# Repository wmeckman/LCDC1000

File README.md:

# LCDC1000
An ESP32 based controller that can drive any kind of LED strip, or motor. Includes microSD, USB-UART, and large voltage range input.

This project started as a Wifi and bluetooth controller that could drive any type of LED strip. LED strip controllers are everywhere, but I wanted a controller that I could customize without using a breadboard. As the project progressed, I wanted this board to be able to drive motors as well. I added a microSD card for file storage, and a USB-UART for debug. Here are the main features:

ESP32 based using MicroPython
Drives Any type of LED strip - RGB, RGBW, WS2812, APA102, Neopixel, etc
Wide input power range: 4.5V to 30V DC.
Input power via Barrel Jack 2.10mm ID (0.083"), 5.50mm OD or Terminal Block.
Reverse polarity input power protection.
Drives 1 stepper motor in full H-bridge configuration.
Drives 2 bipolar DC motors in half H-bridge configuration.
Drives 4 Unipolar DC Motors.
Additional outputs for servo motors available.
Current sense for motor/LED drivers.
Outputs on terminal blocks.

Power: 4.5V-30V DC power can be applied either through the barrel jack or the terminal block (not both). An on-board regulator is used to create the 3.3V necessary for the ESP32, MicroUSB, and USB-UART.  The power input on J6 and J5 is equal to the power output on J7.  Use a power supply that is designed to drive what is connected on the output.  For example, if driving a 12V RGB LED strip, use a 12V power supply.  

To use the board, connect whatever you're controlling (LED, motor, etc) to the terminal blocks (J3, J4, J7), then apply power to J5 or J6.  The 'connection notes' section provides more in depth instruction by device.

Pinouts

J6 Barrel Jack Input Power

    Pin:  +Vin 4.5V to 30V
    Shield:  Ground

J5 Input Power Terminal Block

    1:  +Vin 4.5V to 30V
    2:  +Vin 4.5V to 30V
    3:  Ground
    4:  Ground

J7 Output Power Terminal Block

    1:  +Vout
    2:  +Vout
    3:  Ground
    4:  Ground

J3, J4, J8 High Current Motor and RGB, RGBW LED Drive Terminal Block

    J3-1:  Power Out
    J3-8:  Drive1Out1
    J4-1:  Drive1Out2
    J4-2:  Drive2Out1
    J8-1:  Drive2Out2
    J8-2:  Ground

J9 and J10:  SPI, and PWM Drive Signals for Servo Motor, individually addressable LED's Terminal Block

    J9-1:  GPIO_2 (ESP32 IO2)
    J9-2:  GPIO_5 (ESP32 IO5) 
    J10-1:  LED_DATA (ESP IO19)
    J10-2:  LED_CLK (ESP IO18)

Test Point Header Pins

    TP1:  TDI_SD_MISO - Primarily used to SD card, but can be used for JTAG
    TP2:  TDO_SD_CD - Primarily used to SD card, but can be used for JTAG
    TP3:  TMS_SD_CLK - Primarily used to SD card, but can be used for JTAG
    TP4:  TCK_SD_MOSI - Primarily used to SD card, but can be used for JTAG
    TP5:  ESP32 Enable
    TP7:  IO17
    TP8:  GPIO_0 - ESP32 IO0
    TP9:  ESP32 IO35
    TP10:  ESP32 SENSOR_VP
    TP11:  ESP32 SENSOR_VN
    TP12:  +Vout
    TP13:  +Vout
    TP14:  +Vout
    TP17:  GND
    TP18:  GND
    TP19:  GND
    USBPWR_TP:  USB Power 

Note:  TP2, TP7, TP8 are arranged on the PCB with TP12-TP14, and TP17-TP19 to be compatible with servo motor connections.

---------------------------------------------------------------------------------------------------

Connection Notes:  Overview of connections for various devices

Individually addressable LED's - WS2812, NeoPixel, etc.

    J7-1:  LED Power
    J7-4:  LED Ground
    J9-1:  LED Data

Individually Addressable LED's - APA102, SK9822, DotStar, etc.

    J7-1:  LED Power
    J7-4:  LED Ground
    J10-1:  LED Data
    J10-2:  LED Clock

J10-1, and J10-2 are connected to the ESP32 SPI bus.  This provides the highest speed possible.  Additional LED strips can be connected using lower speed GPIO pins.  

Low speed GPIO connection example:

    J7-2:  LED Power
    J7-3:  LED Ground
    J9-1:  LED Data
    J9-2:  LED Clock

RGB Strips

    J7-1: LED Power
    J3-1: R
    J3-2: G
    J3-3: B

RGBW Strips

    J3-1: LED Power
    J3-2: R
    J4-1: G
    J4-2: B
    J8-1: W

Bipolar DC Stepper Motor

    J3-2:  Coil1+
    J4-1:  Coil1-
    J4-2:  Coil2+
    J8-1:  Coil2-

Unipolar DC Stepper Motor 5 Wire

    J3-2:  Coil 1
    J4-1:  Coil 2
    J4-2:  Coil 3
    J8-1:  Coil 4
    J7-3:  Ground

Unipolar DC Stepper Motor 6 Wire

    J3-2:  Coil 1
    J4-1:  Coil 2
    J4-2:  Coil 3
    J8-1:  Coil 4
    J7-3:  Ground
    J7-4:  Ground

DC Motor Unidirectional  :  Connect up to 4

    Use J3-2 or J4-1 or J4-2 or J8-1 for (+) wire
    Use J7-3 or J7-4 for (-) wire

DC Bidirectional Motor  :  Connect up to 2

    J3-2: Motor 1 (+) 
    J4-1: Motor 1 (-)
    J4-2: Motor 2 (+) 
    J8-1: Motor 2 (-)

Servo Motors

    J7-1 Servo 1 Power +
    J7-3 Servo 1 Power -
    J9-1 Servo 1 Control

    J7-2 Servo 2 Power +
    J7-4 Servo 2 Power -
    J9-2 Servo 2 Control

Additional Servos can be connected on the header pins.

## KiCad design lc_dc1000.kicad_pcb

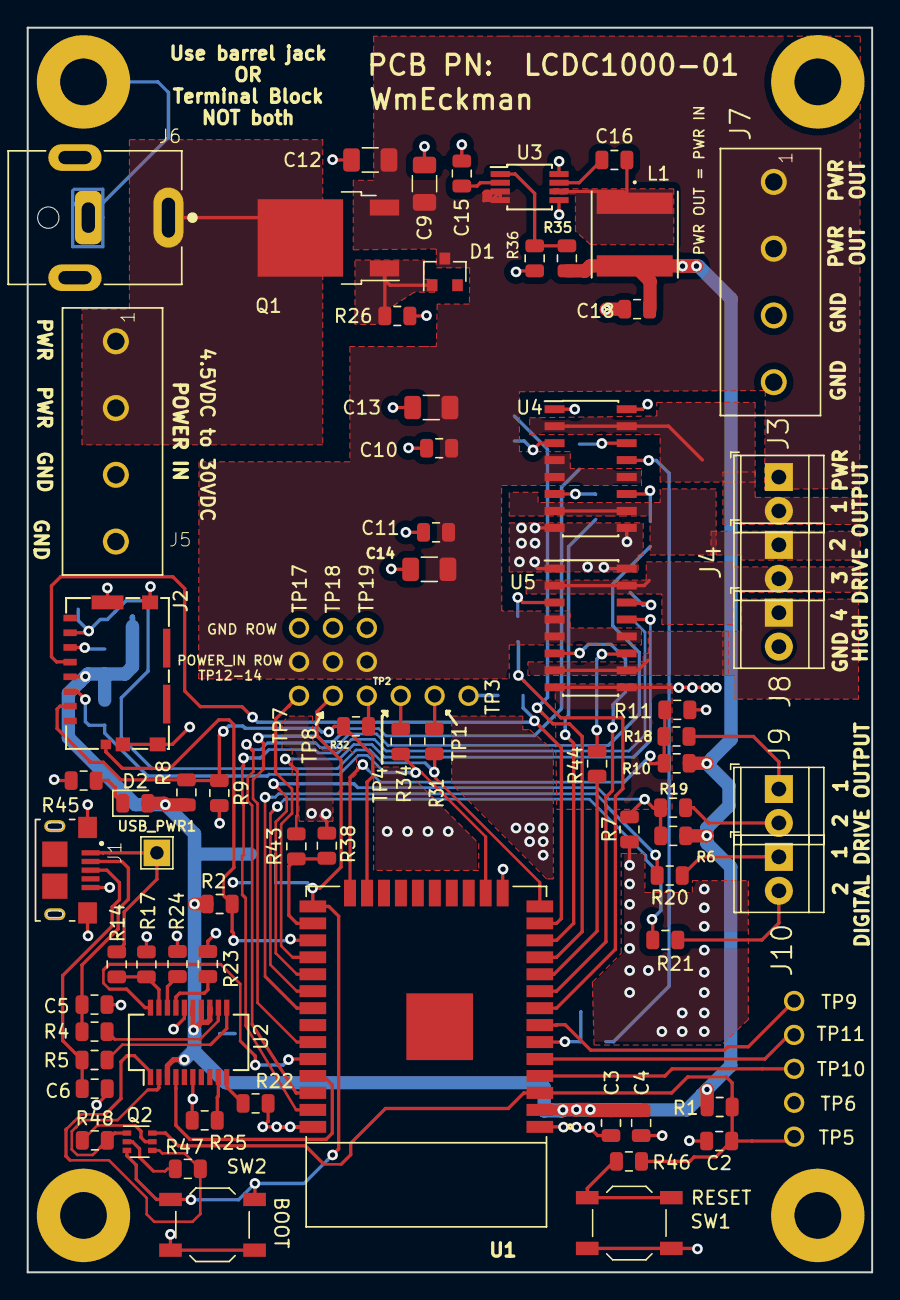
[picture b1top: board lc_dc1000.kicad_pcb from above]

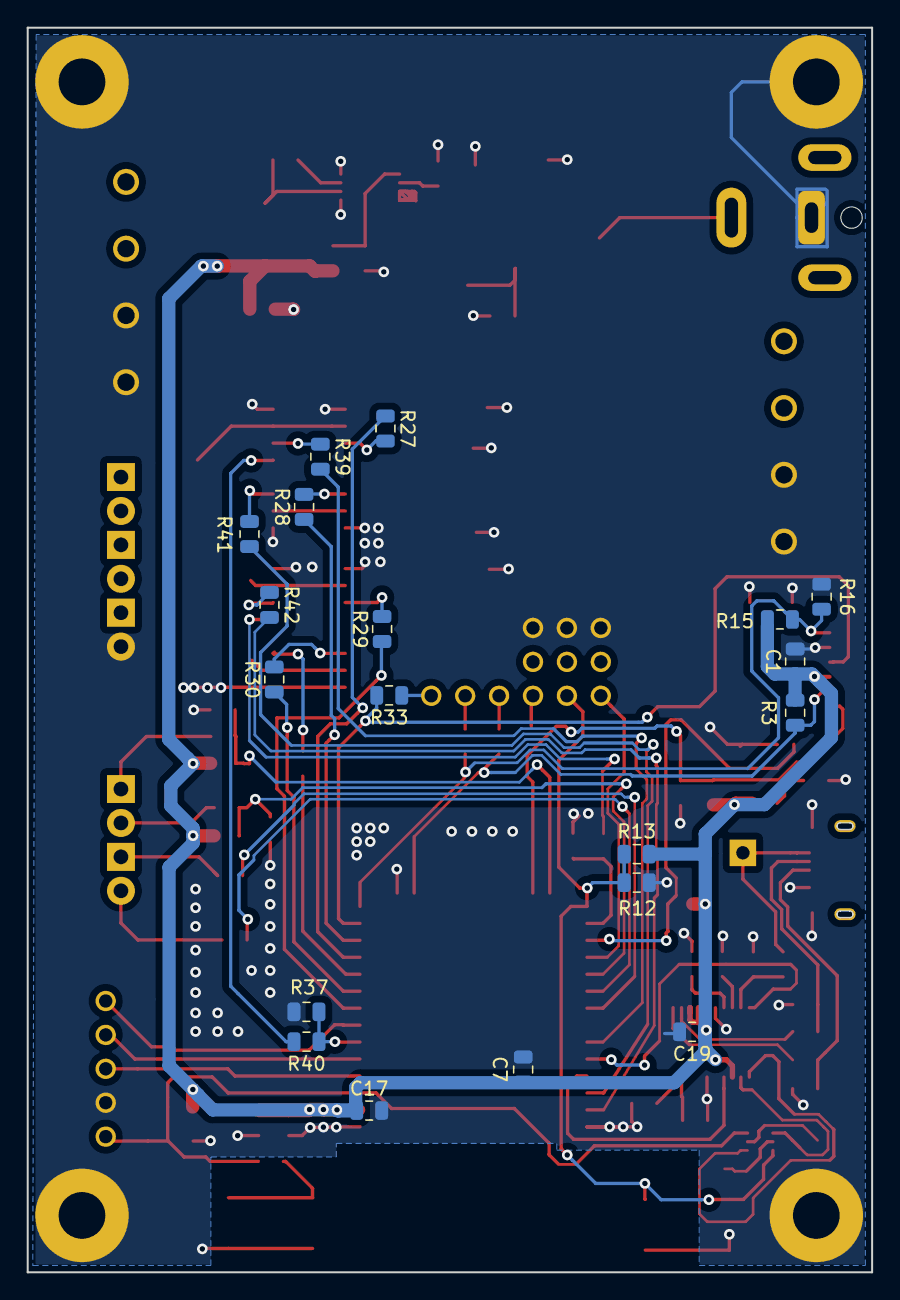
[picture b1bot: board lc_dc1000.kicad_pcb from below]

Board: 2 copper layers, 63.2 x 93.2 mm, 110 parts (19 on the bottom side), 74 nets.

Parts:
C1, C2, C3, C7, C10, C11: 0.1uF; C_0805_2012Metric
C4, C17, C18, C19: 10uF; C_0805_2012Metric
C5, C6: 27pF; C_0805_2012Metric
C9, C12, C13, C14: 4.7uF; C_1206_3216Metric
C15: 1uF; C_0805_2012Metric
C16: .1uF; C_0805_2012Metric
D1: 4.3V; D_SOT-23_ANK
D2: LED; LED_0805_2012Metric
H1, H2, H3, H4: MountingHole_Pad; MountingHole_3.5mm_Pad
J1: 10118193-0001LF; usb
J2: Micro_SD_Card; 1051620001_microsd
J3, J4, J8, J9, J10: Screw_Terminal_01x02; TerminalBlock_TE_282834-2_1x02_P2.54mm_Horizontal
J5, J7: Screw_Terminal_01x04; 691137710004
J6: Barrel_Jack; CUI_PJ-063AH
L1: 15uH; NR6045T150M
Q1: AOD4189; TO-252-2_AOD4189
Q2: MBT3904DW1; SOT-363_SC-70-6
R1, R2, R3, R12, R17, R36, R37, R38, R47, R48: 10k; R_0805_2012Metric
R4, R5: 27; R_0805_2012Metric
R6, R7, R8, R9, R10, R11, R13, R15, R16, R22, R23, R24, R40, R43: DNI; R_0805_2012Metric
R14, R26, R35: 31.6k; R_0805_2012Metric
R18, R19, R20, R21: 10; R_0805_2012Metric
R25, R27, R28, R29, R30, R39, R41, R42, R44, R46: 1k; R_0805_2012Metric
R31, R32, R33, R34, R45: 100; R_0805_2012Metric
SW1, SW2: SW_Push; SW_SPST_TL3342
TP1, TP2, TP3, TP4, TP5, TP6, TP7, TP8, TP9, TP10, TP11, TP12, TP13, TP14, TP17, TP18, TP19: TestPoint; 1mm_tp
U1: ESP32-WROOM-32D; MODULE_ESP32-WROOM-32D
U2: FT231XS; SSOP-20_3.9x8.7mm_P0.635mm
U3: MCP16311MS; MSOP-8_3x3mm_P0.65mm
U4, U5: VNH7100ASTR; SOIC-16_3.9x9.9mm_P1.27mm
USB_PWR1: TestPoint; TestPoint_THTPad_2.0x2.0mm_Drill1.0mm

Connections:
+3V3: C1.1, C3.1, C4.1, C7.1, C17.1, C18.1, C19.1, D2.2, J2.4, L1.2, R1.1, R2.1, R3.1, R6.1, R8.1, R10.1, R12.1, R15.1, R35.1, U1.2, U2.3, U2.13, U2.14, U2.15
/DRV1_CS: R37.1, R40.1, U1.6
/DRV1_INa: R27.1, U1.11
/DRV1_INb: R28.1, U1.12
/DRV1_OUT1: J3.2, U4.2, U4.15
/DRV1_OUT2: J4.1, U4.7, U4.10
/DRV1_PWM: R41.2, U1.36
/DRV1_SEL: R39.2, U1.33
/DRV2_CS: R38.1, R43.1, U1.26
/DRV2_INa: R29.1, U1.8
/DRV2_INb: R30.1, U1.9
/DRV2_OUT1: J4.2, U5.2, U5.15
/DRV2_OUT2: J8.1, U5.7, U5.10
/DRV2_PWM: R44.2, U1.10
/DRV2_SEL: R42.2, U1.37
/DTR: Q2.4, R47.2, U2.1
/EN: C2.1, Q2.6, R1.2, R46.1, TP5.1, U1.3
/GPIO_0: Q2.3, R12.2, R13.1, SW2.1, TP8.1, U1.25
/GPIO_2: R10.2, R11.1, R18.2, U1.24
/GPIO_5: R6.2, R7.1, R19.2, U1.29
/IO17: TP7.1, U1.28
/IO35: TP9.1, U1.7
/LED_CLK: R21.2, U1.30
/LED_DATA: R20.2, U1.31
/PWR: J5.1, J5.2, J6.1, Q1.3
/PWR_RBPROTECTED: C9.1, C10.1, C11.1, C12.1, C13.1, C14.1, D1.1, J3.1, J7.1, J7.2, Q1.2, TP12.1, TP13.1, TP14.1, U3.3, U3.4, U4.4, U4.5, U4.12, U5.4, U5.5, U5.12
/RTS: Q2.1, R48.2, U2.2
/SD_DET: J2.9, R2.2, U1.27
/SENSOR_VN: TP11.1, U1.5
/SENSOR_VP: TP10.1, U1.4
/TCK_SD_MOSI: J2.3, R3.2, R34.2, U1.16
/TDI_SD_MISO: J2.7, R15.2, R16.1, R31.1, U1.14
/TDO_SD_CD: J2.2, R8.2, R9.1, R32.2, U1.23
/TMS_SD_CLK: J2.5, R33.2, U1.13
/UART_RXD: U1.35, U2.4
/UART_TXD: U1.34, U2.20
Earth: C1.2, C2.2, C3.2, C4.2, C5.2, C6.2, C7.2, C9.2, C10.2, C11.2, C12.2, C13.2, C14.2, C15.2, C17.2, C18.2, C19.2, H1.1, H2.1, H3.1, H4.1, J1.5, J1.S1, J1.S2, J2.6, J2.G1, J2.G2, J2.G3, J2.G4, J5.3, J5.4, J6.2, J7.3, J7.4, J8.2, R7.2, R9.2, R11.2, R13.2, R16.2, R17.2, R22.2, R23.2, R24.2, R25.1, R26.2, R36.2, R37.2, R38.2, R45.2, SW1.2, SW2.2, TP6.1, TP17.1, TP18.1, TP19.1, U1.1, U1.15, U1.38, U2.6, U2.16, U3.5, U3.8, U4.1, U4.8, U4.9, U4.16, U5.1, U5.8, U5.9, U5.16
unnamed: C5.1, J1.2, R4.1
unnamed: C6.1, J1.3, R5.1
unnamed: C15.1, U3.2
unnamed: C16.1, L1.1, U3.6
unnamed: C16.2, U3.7
unnamed: D1.2, Q1.1, R26.1
unnamed: D2.1, R45.1
unnamed: J1.1, R14.1, USB_PWR1.1
unnamed: J9.1, R18.1
unnamed: J9.2, R19.1
unnamed: J10.1, R20.1
unnamed: J10.2, R21.1
unnamed: Q2.2, R47.1
unnamed: Q2.5, R48.1
unnamed: R4.2, U2.12
unnamed: R5.2, U2.11
unnamed: R14.2, R17.1, U2.19
unnamed: R22.1, U2.10
unnamed: R23.1, U2.17
unnamed: R24.1, U2.18
unnamed: R25.2, U2.9
unnamed: R27.2, U4.3
unnamed: R28.2, U4.6
unnamed: R29.2, U5.3
unnamed: R30.2, U5.6
unnamed: R31.2, TP1.1
unnamed: R32.1, TP2.1
unnamed: R33.1, TP3.1
unnamed: R34.1, TP4.1
unnamed: R35.2, R36.1, U3.1
unnamed: R39.1, U4.14
unnamed: R40.2, U4.13
unnamed: R41.1, U4.11
unnamed: R42.1, U5.14
unnamed: R43.2, U5.13
unnamed: R44.1, U5.11
unnamed: R46.2, SW1.1

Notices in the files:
parts and their libraries:
Copyright 2016 Accelerated Designs. All rights reserved.
